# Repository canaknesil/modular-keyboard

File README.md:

# modular-keyboard

THIS PROJECT HAS NOT BEEN COMPLETED !!!

Modular keyboard PDB design

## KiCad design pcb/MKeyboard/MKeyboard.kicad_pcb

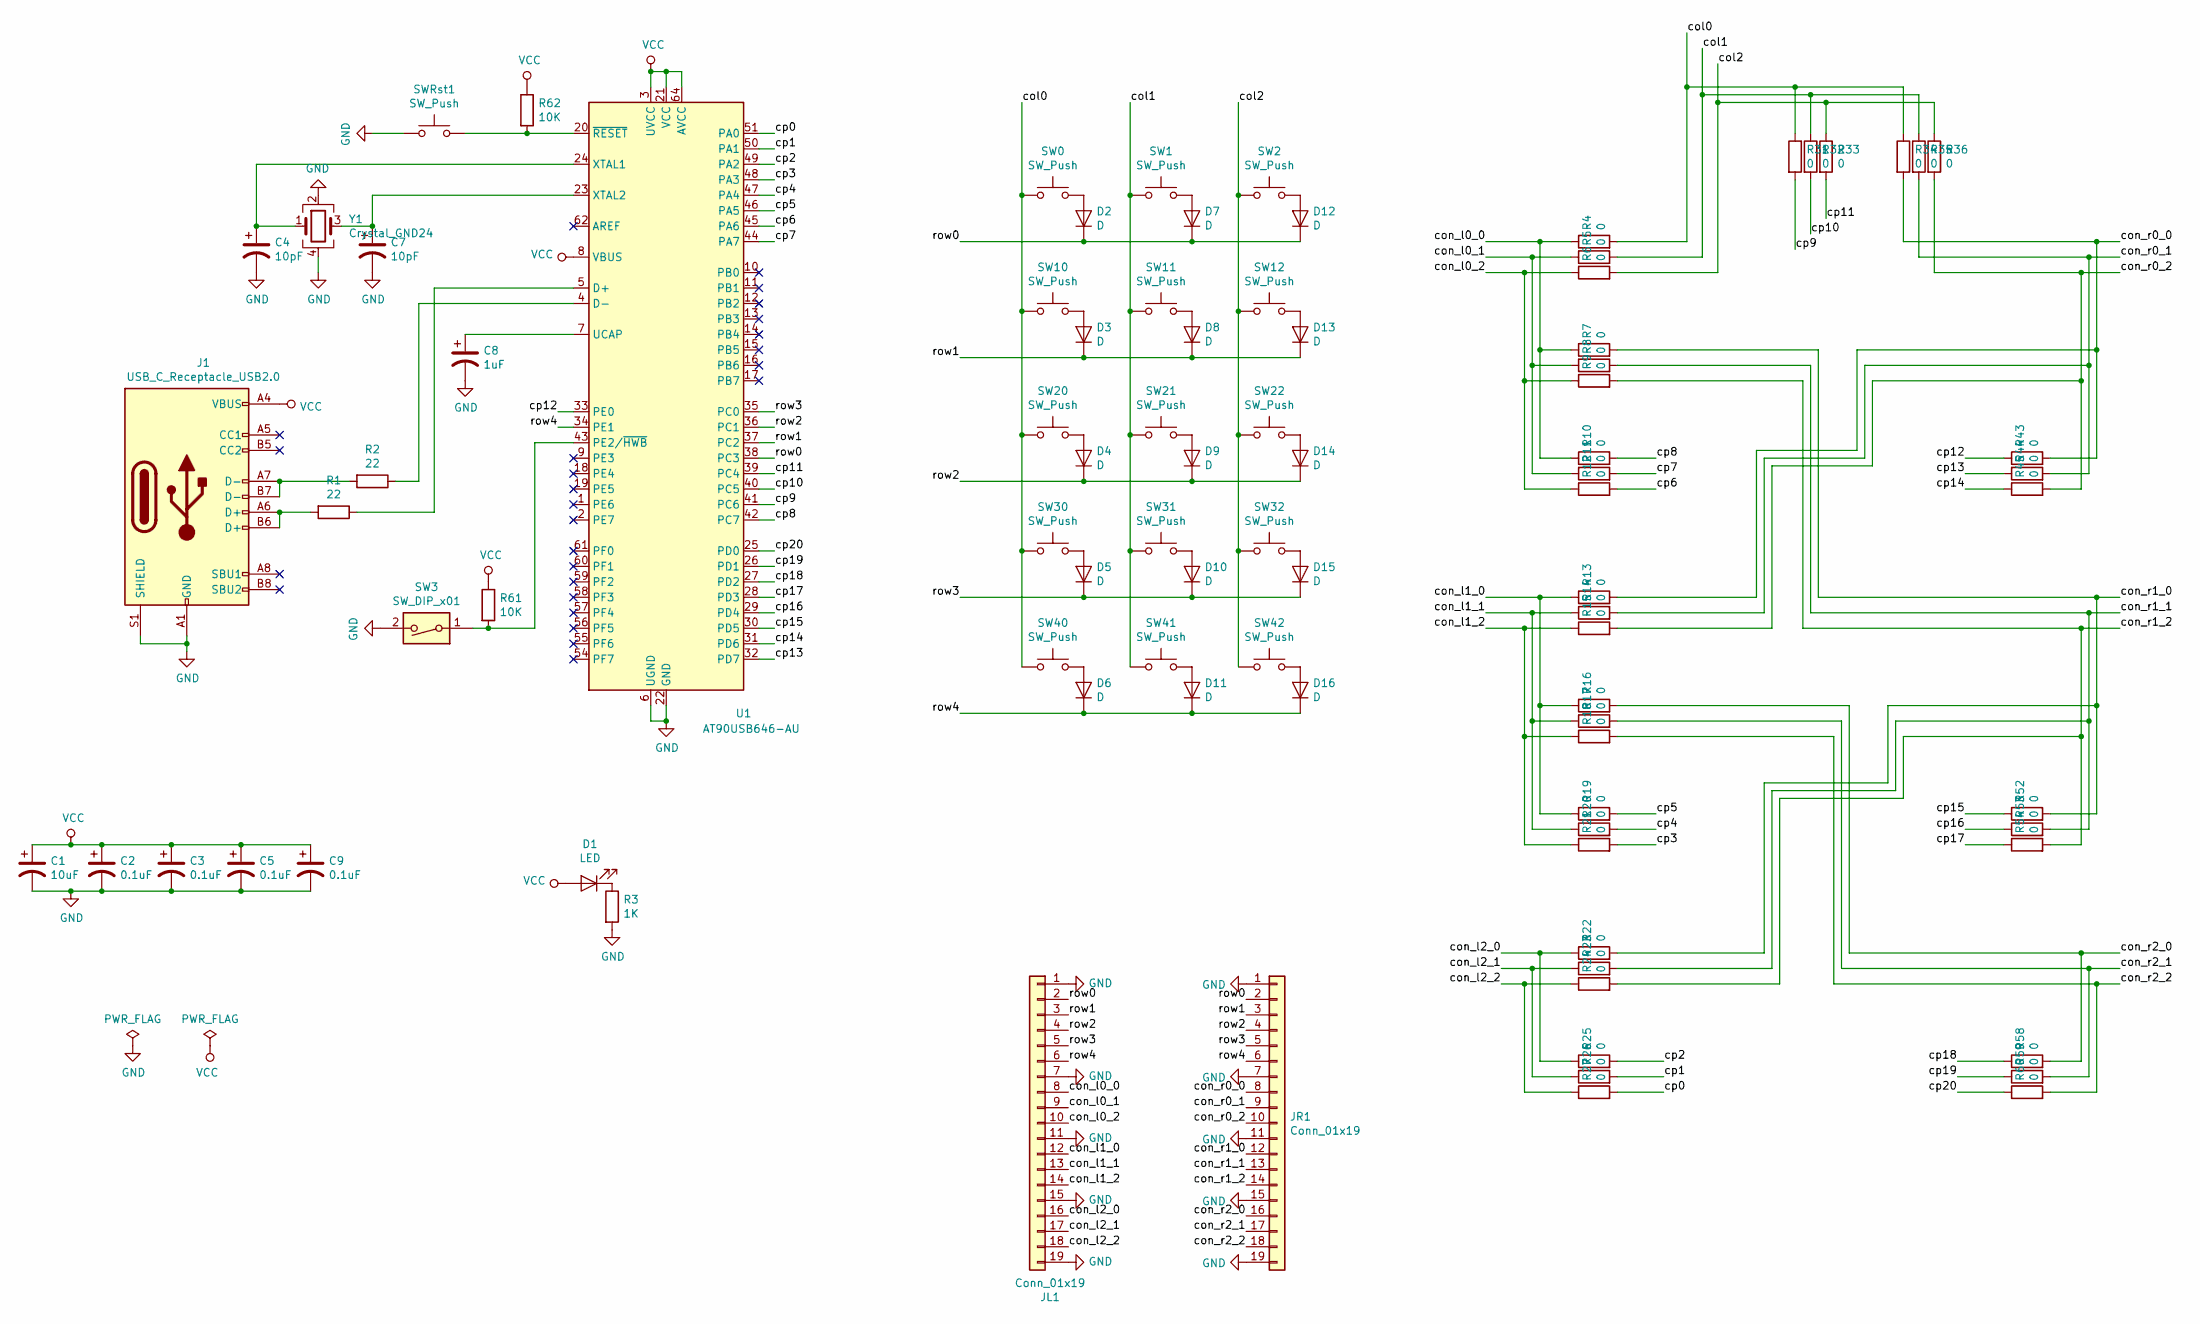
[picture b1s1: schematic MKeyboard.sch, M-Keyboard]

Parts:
C1: 10uF; C_0603_1608Metric_Pad1.05x0.95mm_HandSolder
C2, C3, C5, C9: 0.1uF; C_0603_1608Metric_Pad1.05x0.95mm_HandSolder
C4, C7: 10pF; C_0603_1608Metric_Pad1.05x0.95mm_HandSolder
C8: 1uF; C_0603_1608Metric_Pad1.05x0.95mm_HandSolder
D1: LED; LED_0603_1608Metric_Pad1.05x0.95mm_HandSolder
D2, D3, D4, D5, D6, D7, D8, D9, D10, D11, D12, D13, D14, D15, D16: D; D_1206_3216Metric_Pad1.42x1.75mm_HandSolder
J1: USB_C_Receptacle_USB2.0; USB_C_Receptacle_GCT_USB4085
JL1: Conn_01x19; PinSocket_1x19_P2.54mm_Horizontal
JR1: Conn_01x19; PinHeader_1x19_P2.54mm_Horizontal
R1, R2: 22; R_0603_1608Metric_Pad1.05x0.95mm_HandSolder
R3: 1K; R_0603_1608Metric_Pad1.05x0.95mm_HandSolder
R4, R5, R6, R7, R8, R9, R10, R11, R12, R13, R14, R15, R16, R17, R18, R19, R20, R21, R22, R23, R24, R25, R26, R27, R31, R32, R33, R34, R35, R36, R43, R44, R45, R52, R53, R54, R58, R59, R60: 0; R_0603_1608Metric_Pad1.05x0.95mm_HandSolder
R61, R62: 10K; R_0603_1608Metric_Pad1.05x0.95mm_HandSolder
SW0, SW1, SW2, SW10, SW11, SW12, SW20, SW21, SW22, SW30, SW31, SW32, SW40, SW41, SW42: SW_Push; SW_Cherry_MX_1.00u_PCB
SW3: SW_DIP_x01; SW_DIP_SPSTx01_Slide_6.7x4.1mm_W8.61mm_P2.54mm_LowProfile
SWRst1: SW_Push; SW_Push_1P1T_NO_6x6mm_H9.5mm
U1: AT90USB646-AU; TQFP-64_14x14mm_P0.8mm
Y1: Crystal_GND24; Crystal_SMD_0603-4Pin_6.0x3.5mm_HandSoldering

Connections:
/col0: R4.2, R31.1, R34.1, SW0.1, SW10.1, SW20.1, SW30.1, SW40.1
/col1: R5.2, R32.1, R35.1, SW1.1, SW11.1, SW21.1, SW31.1, SW41.1
/col2: R6.2, R33.1, R36.1, SW2.1, SW12.1, SW22.1, SW32.1, SW42.1
/con_l0_0: JL1.8, R4.1, R7.1, R10.1
/con_l0_1: JL1.9, R5.1, R8.1, R11.1
/con_l0_2: JL1.10, R6.1, R9.1, R12.1
/con_l1_0: JL1.12, R13.1, R16.1, R19.1
/con_l1_1: JL1.13, R14.1, R17.1, R20.1
/con_l1_2: JL1.14, R15.1, R18.1, R21.1
/con_l2_0: JL1.16, R22.1, R25.1
/con_l2_1: JL1.17, R23.1, R26.1
/con_l2_2: JL1.18, R24.1, R27.1
/con_r0_0: JR1.8, R13.2, R34.2, R43.2
/con_r0_1: JR1.9, R14.2, R35.2, R44.2
/con_r0_2: JR1.10, R15.2, R36.2, R45.2
/con_r1_0: JR1.12, R7.2, R22.2, R52.2
/con_r1_1: JR1.13, R8.2, R23.2, R53.2
/con_r1_2: JR1.14, R9.2, R24.2, R54.2
/con_r2_0: JR1.16, R16.2, R58.2
/con_r2_1: JR1.17, R17.2, R59.2
/con_r2_2: JR1.18, R18.2, R60.2
/cp0: R27.2, U1.51 (PA0)
/cp1: R26.2, U1.50 (PA1)
/cp2: R25.2, U1.49 (PA2)
/cp3: R21.2, U1.48 (PA3)
/cp4: R20.2, U1.47 (PA4)
/cp5: R19.2, U1.46 (PA5)
/cp6: R12.2, U1.45 (PA6)
/cp7: R11.2, U1.44 (PA7)
/cp8: R10.2, U1.42 (PC7)
/cp9: R31.2, U1.41 (PC6)
/cp10: R32.2, U1.40 (PC5)
/cp11: R33.2, U1.39 (PC4)
/cp12: R43.1, U1.33 (PE0)
/cp13: R44.1, U1.32 (PD7)
/cp14: R45.1, U1.31 (PD6)
/cp15: R52.1, U1.30 (PD5)
/cp16: R53.1, U1.29 (PD4)
/cp17: R54.1, U1.28 (PD3)
/cp18: R58.1, U1.27 (PD2)
/cp19: R59.1, U1.26 (PD1)
/cp20: R60.1, U1.25 (PD0)
/row0: D2.1 (K), D7.1 (K), D12.1 (K), JL1.2, JR1.2, U1.38 (PC3)
/row1: D3.1 (K), D8.1 (K), D13.1 (K), JL1.3, JR1.3, U1.37 (PC2)
/row2: D4.1 (K), D9.1 (K), D14.1 (K), JL1.4, JR1.4, U1.36 (PC1)
/row3: D5.1 (K), D10.1 (K), D15.1 (K), JL1.5, JR1.5, U1.35 (PC0)
/row4: D6.1 (K), D11.1 (K), D16.1 (K), JL1.6, JR1.6, U1.34 (PE1)
GND: C1.2, C2.2, C3.2, C4.2, C5.2, C7.2, C8.2, C9.2, J1.A1 (GND), J1.A12 (GND), J1.B1 (GND), J1.B12 (GND), J1.S1 (SHIELD), JL1.1, JL1.7, JL1.11, JL1.15, JL1.19, JR1.1, JR1.7, JR1.11, JR1.15, JR1.19, R3.2, SW3.2, SWRst1.1, U1.6 (UGND), U1.22 (GND), U1.53 (GND), U1.63 (GND), Y1.2, Y1.4
unnamed: C4.1, U1.24 (XTAL1), Y1.1
unnamed: C7.1, U1.23 (XTAL2), Y1.3
unnamed: C8.1, U1.7 (UCAP)
unnamed: D1.1 (K), R3.1
unnamed: D2.2 (A), SW0.2
unnamed: D3.2 (A), SW10.2
unnamed: D4.2 (A), SW20.2
unnamed: D5.2 (A), SW30.2
unnamed: D6.2 (A), SW40.2
unnamed: D7.2 (A), SW1.2
unnamed: D8.2 (A), SW11.2
unnamed: D9.2 (A), SW21.2
unnamed: D10.2 (A), SW31.2
unnamed: D11.2 (A), SW41.2
unnamed: D12.2 (A), SW2.2
unnamed: D13.2 (A), SW12.2
unnamed: D14.2 (A), SW22.2
unnamed: D15.2 (A), SW32.2
unnamed: D16.2 (A), SW42.2
unnamed: J1.A6 (D+), J1.B6 (D+), R1.2
unnamed: J1.A7 (D-), J1.B7 (D-), R2.2
unnamed: R1.1, U1.5 (D+)
unnamed: R2.1, U1.4 (D-)
unnamed: R61.2, SW3.1, U1.43 (PE2/~HWB)
unnamed: R62.2, SWRst1.2, U1.20 (~RESET)
VCC: C1.1, C2.1, C3.1, C5.1, C9.1, D1.2 (A), J1.A4 (VBUS), J1.A9 (VBUS), J1.B4 (VBUS), J1.B9 (VBUS), R61.1, R62.1, U1.3 (UVCC), U1.8 (VBUS), U1.21 (VCC), U1.52 (VCC), U1.64 (AVCC)

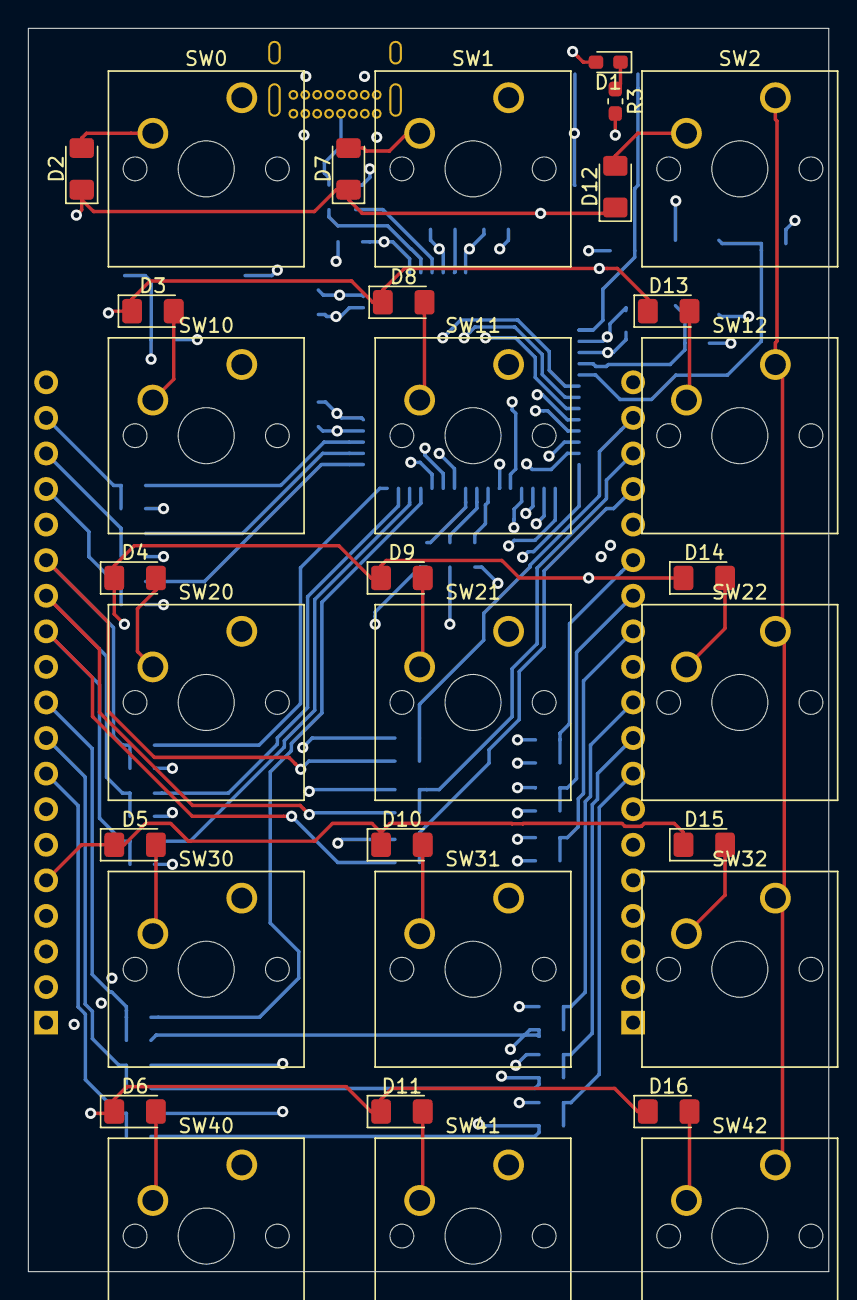
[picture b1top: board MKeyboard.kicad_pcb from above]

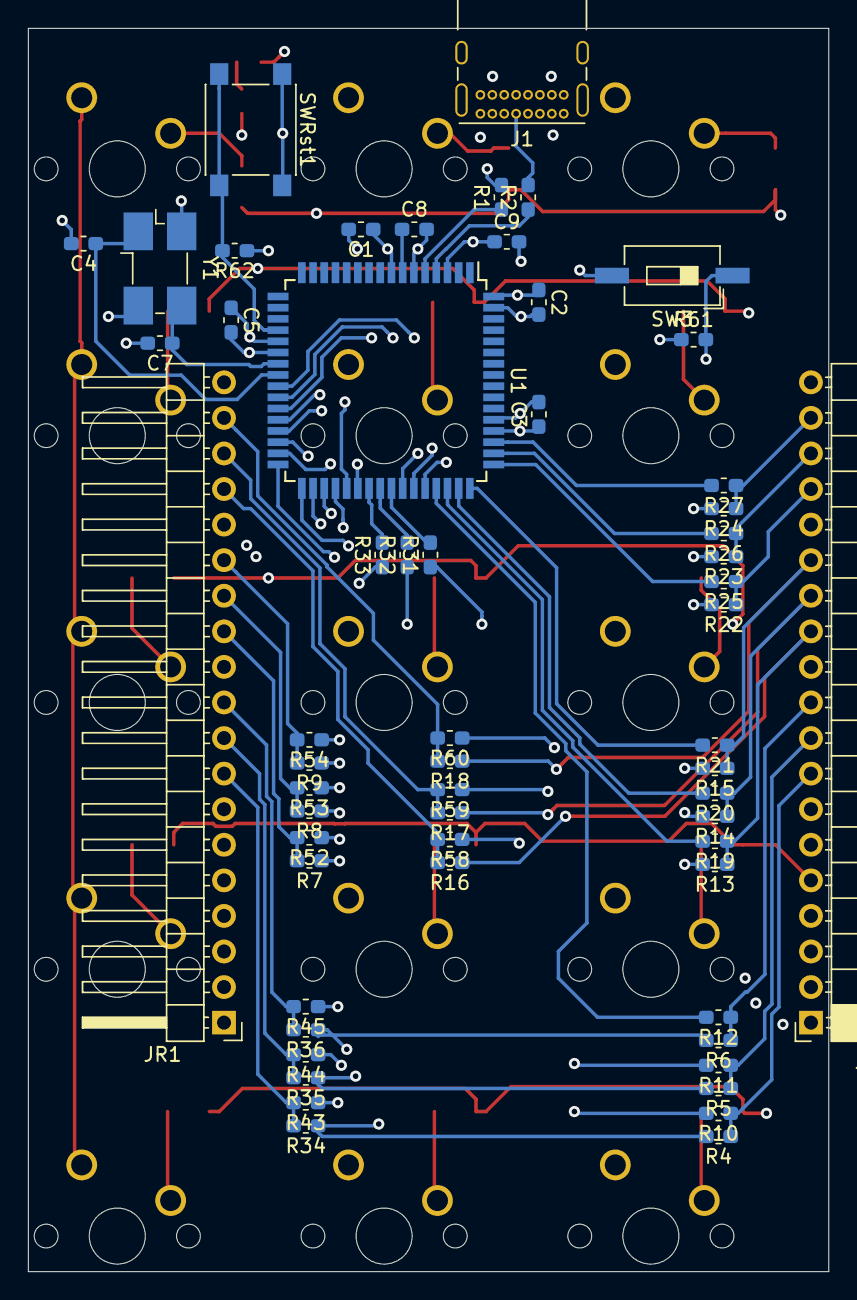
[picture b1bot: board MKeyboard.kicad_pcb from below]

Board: 6 copper layers, 57.1 x 88.8 mm, 90 parts (58 on the bottom side), 74 nets.

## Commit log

2021-09-21 schematics
2021-09-30 0-ohm resisters instead of dip-switches, component placement in PCB layout.
2021-10-07 placement
2021-10-15 smaller components, positioning
2021-10-18 Most 0-ohm resisters are routed.
2021-10-29 Most of the non-power routing.
2021-10-29 power planes and all components routed
2021-10-29 fixed orientation of left connector
2021-11-04 create license
